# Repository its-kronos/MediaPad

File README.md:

# MediaPad

# Overview
- The MediaPad is a macropad made for the Hackclub program Hackpad.
- The macroboard features multiple buttons to control Youtube-based media, including functions such as going to the previous video, rewinding, pausing, skipping 5 seconds, and going to the next video.
- Additionally, there is a rotary encoder to control the volume, and pressing it allows the volume to be locked to prevent accidental changes.
- Similarly, a board-lock button exists to lock the keys that move to a different video, allowing only the inputs related to volume or time changing within the current video
- Features an LED that could be used for debugging or other purposes if neccessary \
*Note that the Models folder is for models used in the KiCad PCB rendering

# Demo

https://vimeo.com/1098898996

# Case
- Includes a plate for switch stability, and everything is held together by M3 screws with threading in the plastic through the 3D-printed parts, but not the PCB
- Plate is top-mounted
- Also includes a cover for the rotary encoder for visuals and use

# PCB
## Schematic:

## Front:

## Back: 
Nothing to see here (except traces)

# Firmware
- Uses KMK with CircuitPython, as included in the code folder. Only the custom code is included in the production folder.
# Lessons Learned
- First time using Fusion!!!!!
- Learned a lot about keyboards and how they work, a full-sized keyboard would 100% be made in the future
- Learned how to add models to PCB
- Learned a lot about 3D modeling
# BOM
- (1) PCB
- (1) EC11 Rotary Encoder
- (1) Rotary Encoder Cap (3D printed part)
- (1) Case Bottom
- (1) Case Top
- (1) Case Plate
- (8) M3x16MM Screws
- (1) XIAO RP2040
- (6) Cherry MX Switches
- (6) DSA Keycaps
- (1) SK6812 MINI-E LED

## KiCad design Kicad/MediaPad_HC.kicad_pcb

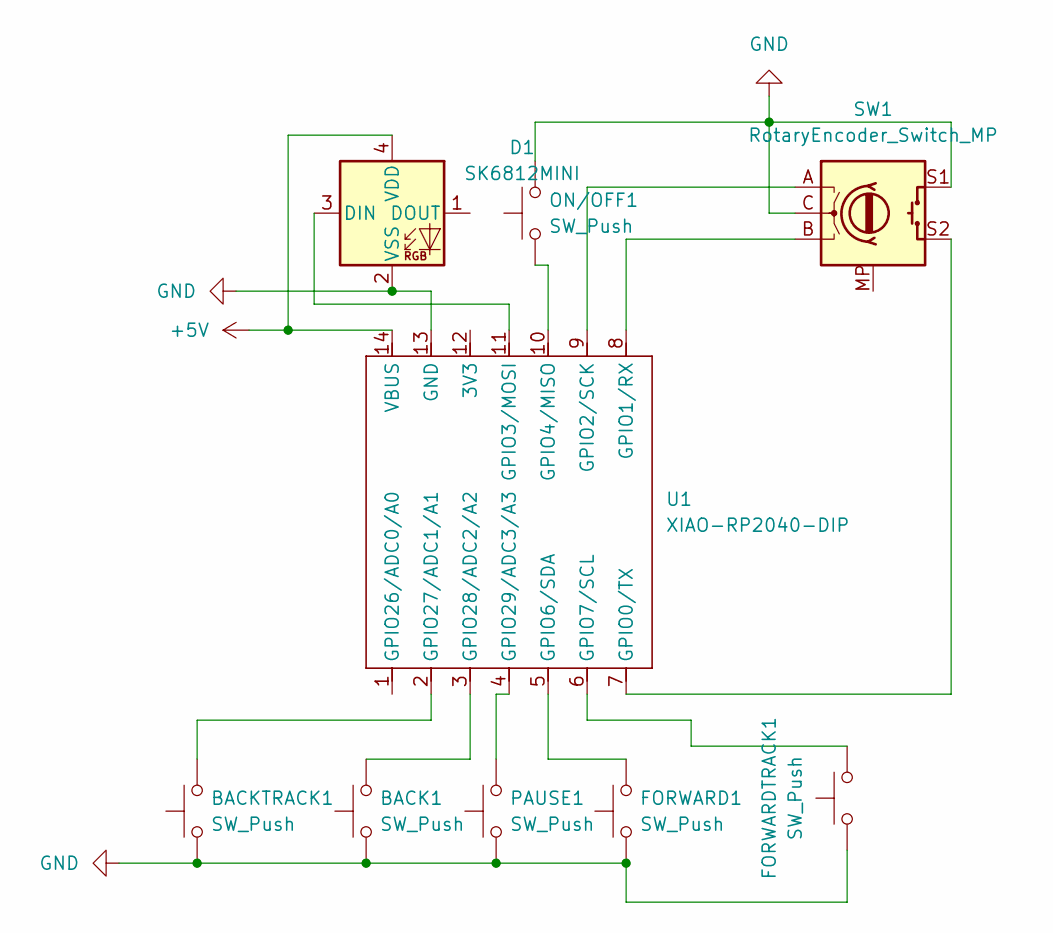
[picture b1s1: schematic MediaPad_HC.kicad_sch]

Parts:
BACK1: SW_Push; SW_Cherry_MX_1.00u_PCB
BACKTRACK1: SW_Push; SW_Cherry_MX_1.00u_PCB
D1: SK6812MINI; LED_SK6812MINI_PLCC4_3.5x3.5mm_P1.75mm
FORWARD1: SW_Push; SW_Cherry_MX_1.00u_PCB
FORWARDTRACK1: SW_Push; SW_Cherry_MX_1.00u_PCB
ON/OFF1: SW_Push; SW_Cherry_MX_1.00u_PCB
PAUSE1: SW_Push; SW_Cherry_MX_1.00u_PCB
SW1: RotaryEncoder_Switch_MP; RotaryEncoder_Alps_EC11E-Switch_Vertical_H20mm
U1: XIAO-RP2040-DIP

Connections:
+5V: D1.4 (VDD), U1.14 (VBUS)
GND: BACK1.1, BACKTRACK1.1, D1.2 (VSS), FORWARD1.1, FORWARDTRACK1.1, ON/OFF1.2, PAUSE1.1, SW1.C, SW1.S1, U1.13 (GND)
unnamed: D1.3 (DIN), U1.11 (GPIO3/MOSI)
unnamed: SW1.S2, U1.7 (GPIO0/TX)
unnamed: SW1.B, U1.8 (GPIO1/RX)
unnamed: SW1.A, U1.9 (GPIO2/SCK)
unnamed: ON/OFF1.1, U1.10 (GPIO4/MISO)
unnamed: FORWARD1.2, U1.5 (GPIO6/SDA)
unnamed: FORWARDTRACK1.2, U1.6 (GPIO7/SCL)
unnamed: BACKTRACK1.2, U1.2 (GPIO27/ADC1/A1)
unnamed: BACK1.2, U1.3 (GPIO28/ADC2/A2)
unnamed: PAUSE1.2, U1.4 (GPIO29/ADC3/A3)

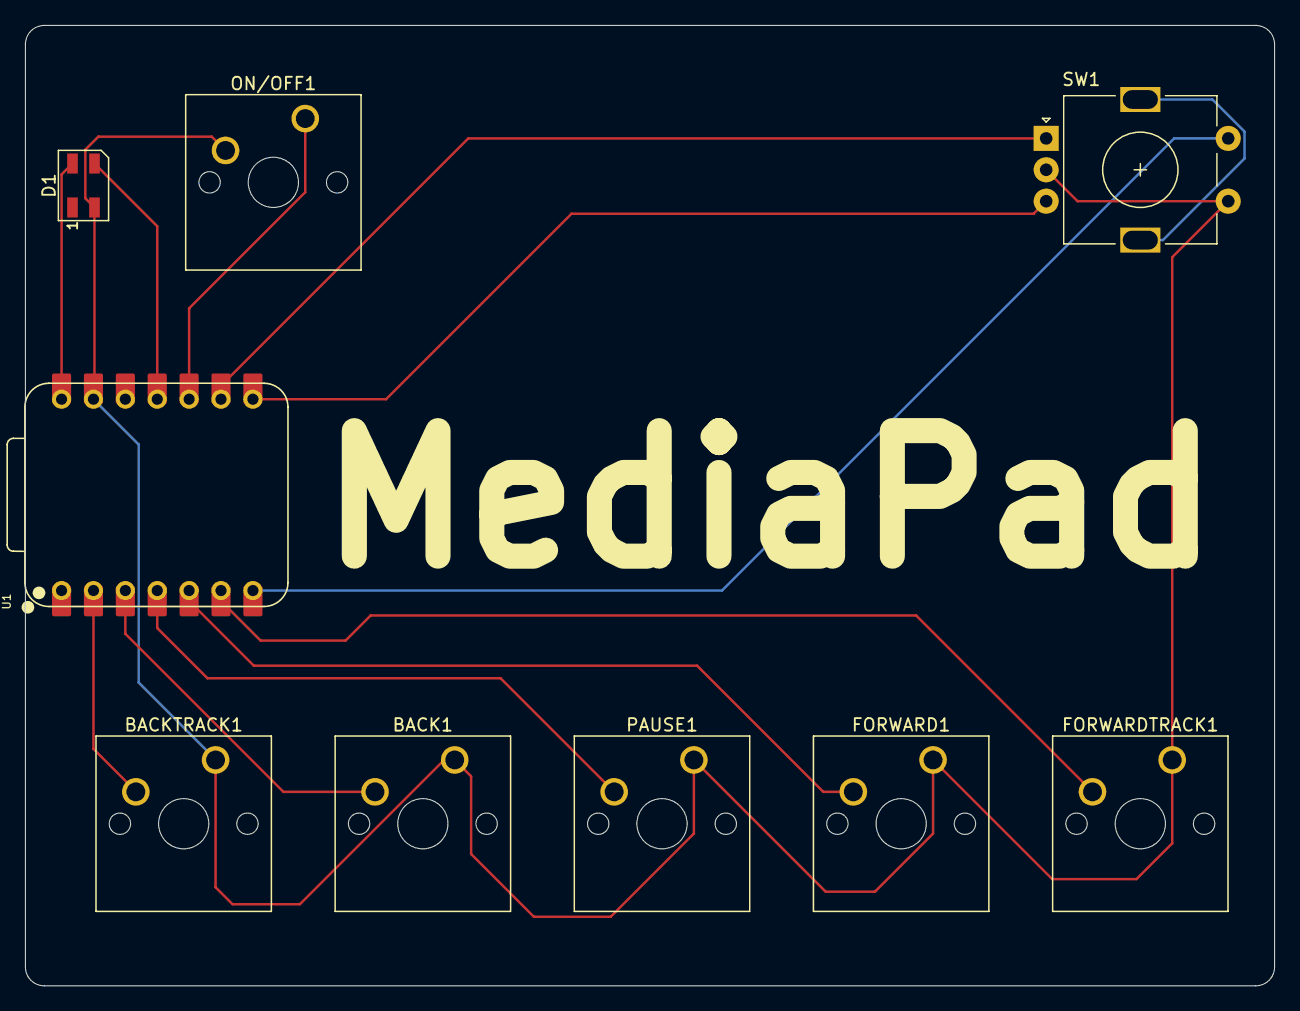
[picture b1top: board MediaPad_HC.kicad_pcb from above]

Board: 2 copper layers, 99.5 x 76.5 mm, 9 parts (0 on the bottom side), 12 nets.

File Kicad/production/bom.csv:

Designator,Footprint,Quantity,Value,LCSC Part #
"BACK1, BACKTRACK1, FORWARD1, FORWARDTRACK1, ON/OFF1, PAUSE1",SW_Cherry_MX_1.00u_PCB,6,SW_Push,
D1,LED_SK6812MINI_PLCC4_3.5x3.5mm_P1.75mm,1,SK6812MINI,
SW1,RotaryEncoder_Alps_EC11E-Switch_Vertical_H20mm,1,RotaryEncoder_Switch_MP,
U1,XIAO-RP2040-DIP,1,XIAO-RP2040-DIP,

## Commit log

2025-06-08 rename
2025-06-08 add production
2025-06-29 make code work!
2025-07-04 fix code so that rotary encoder works
2025-07-04 Update README.md - add demo
2025-08-01 Update README.md - add project picture to readme
